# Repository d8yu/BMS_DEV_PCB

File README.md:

<h1>BMS Development Board</h1>

<h2>Preview</h2>
<h3>PCB Schematic</h3>

<h3>PCB Render</h3>

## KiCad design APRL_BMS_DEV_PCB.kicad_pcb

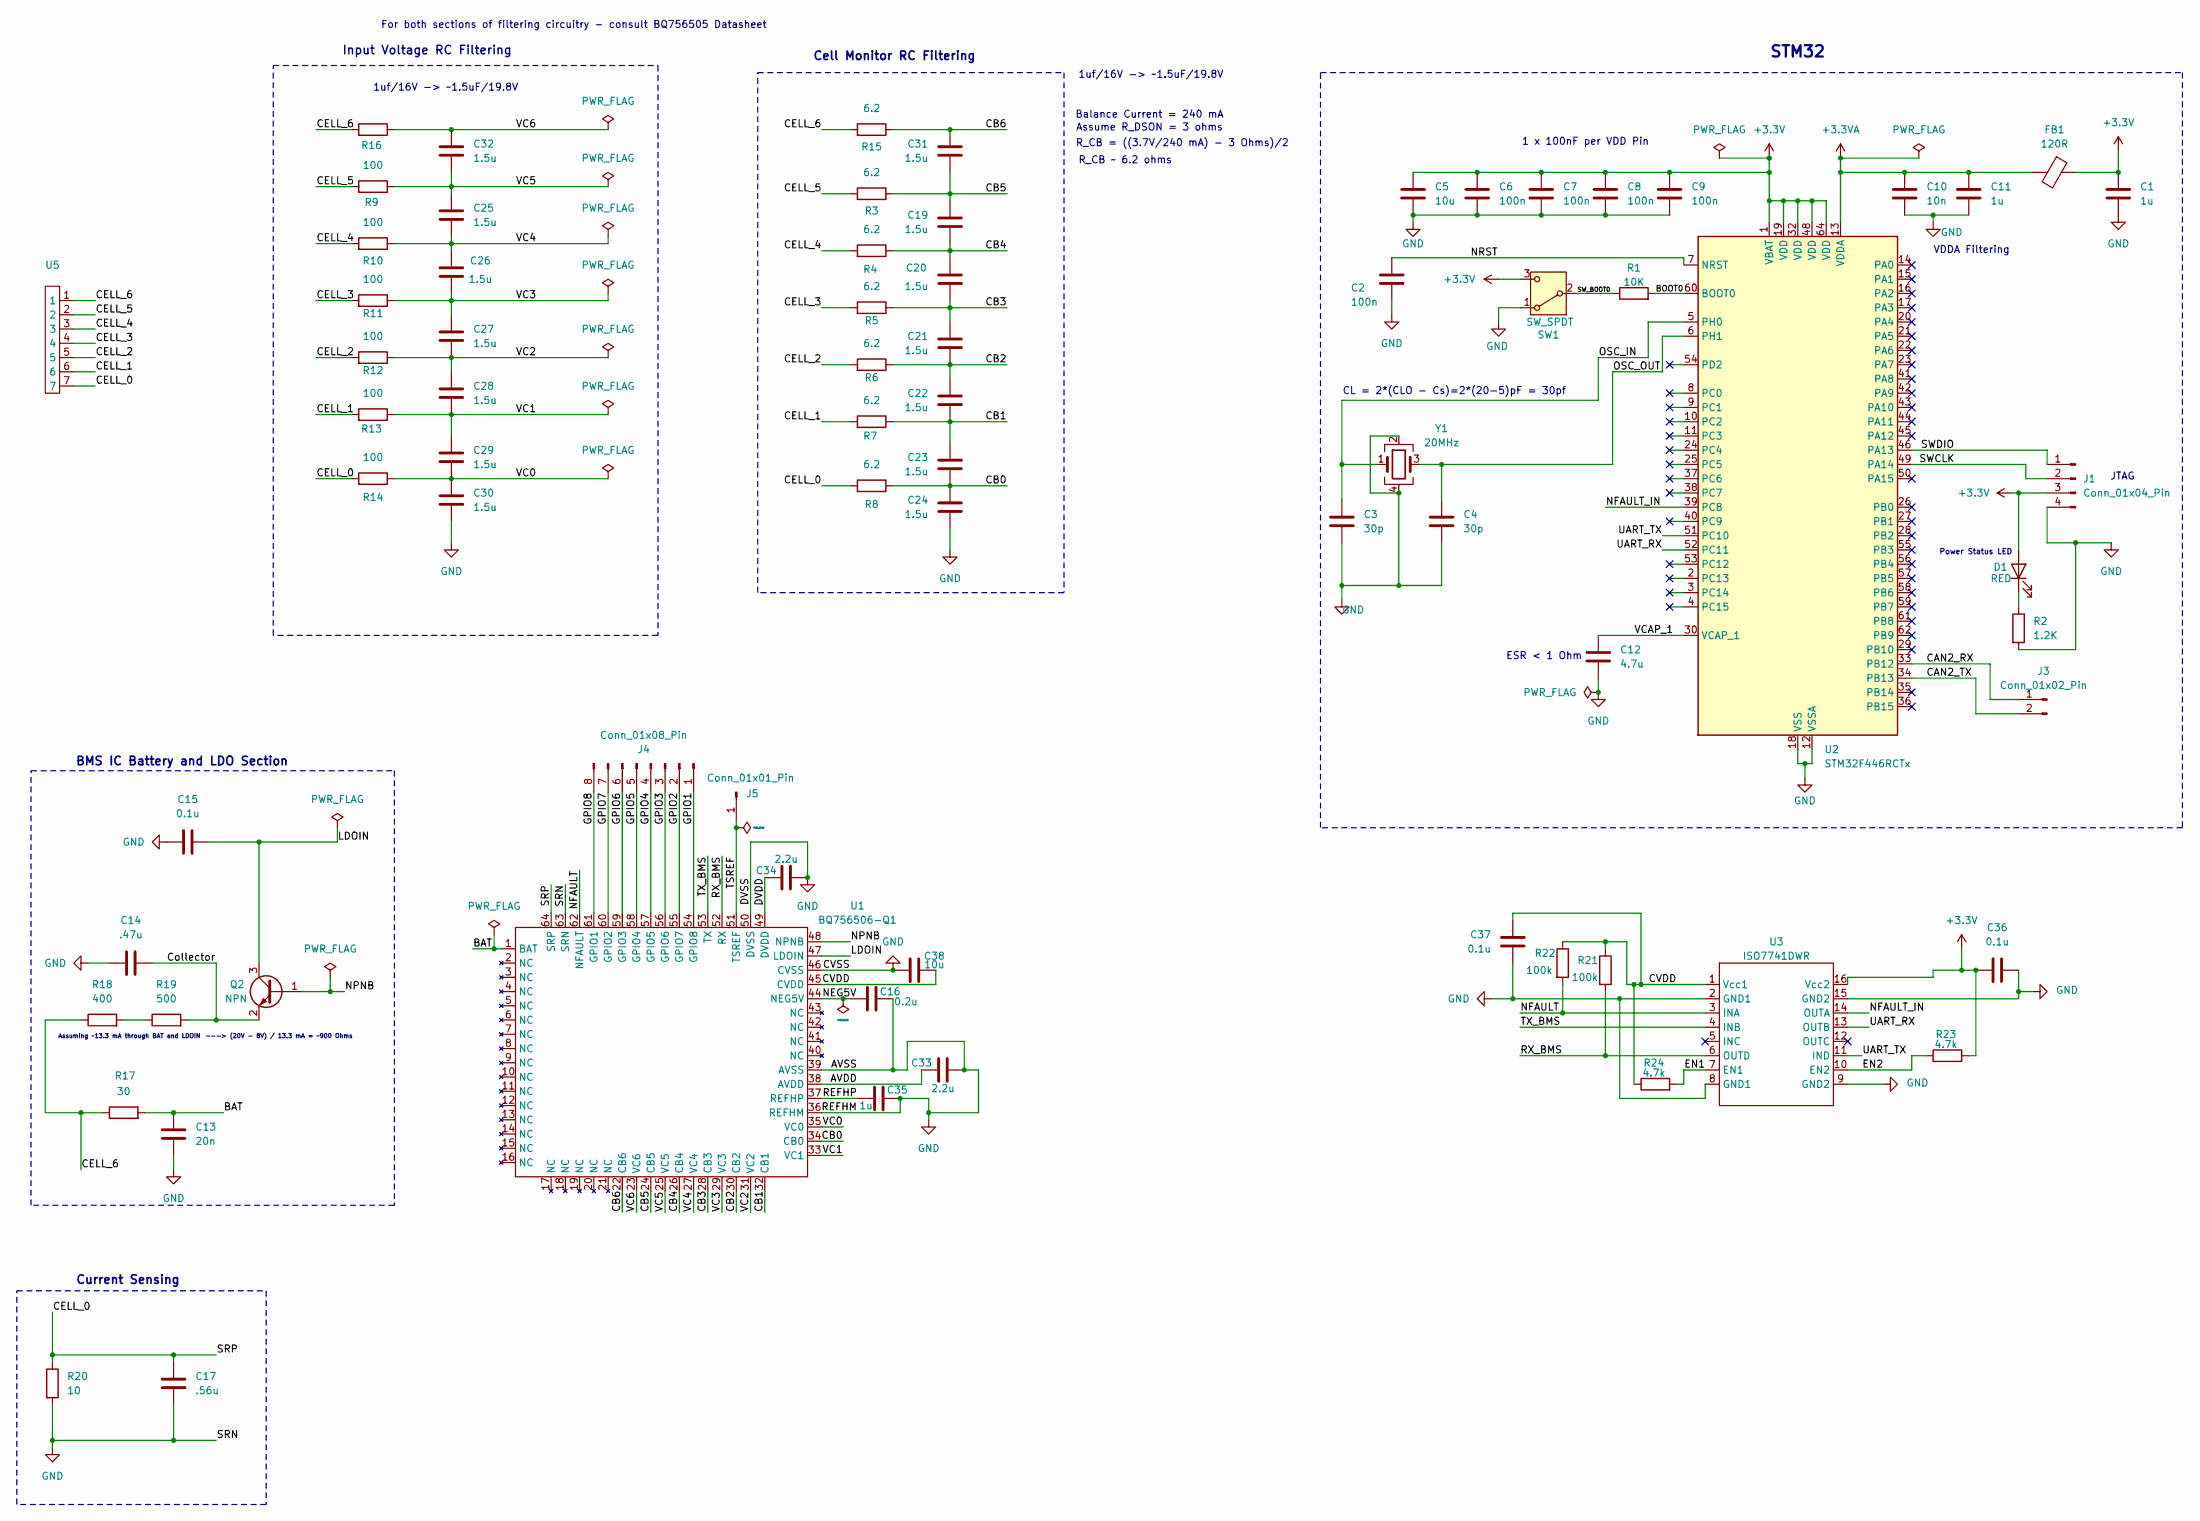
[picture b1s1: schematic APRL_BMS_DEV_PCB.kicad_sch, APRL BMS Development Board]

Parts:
C1, C11, C35: 1u; C_0603_1608Metric
C2, C6, C7, C8, C9: 100n; C_0603_1608Metric
C3, C4: 30p; C_0603_1608Metric
C5, C38: 10u; C_0603_1608Metric
C10: 10n; C_0603_1608Metric
C12: 4.7u; C_0603_1608Metric
C13: 20n; C_0603_1608Metric
C14: .47u; C_0603_1608Metric
C15, C36, C37: 0.1u; C_0603_1608Metric
C16: 0.2u; C_0603_1608Metric
C17: .56u; C_0603_1608Metric
C19, C20, C21, C22, C23, C24, C25, C26, C27, C28, C29, C30, C31, C32: 1.5u; C_0402_1005Metric
C33, C34: 2.2u; C_0603_1608Metric
D1: RED; LED_0603_1608Metric
FB1: 120R; R_0603_1608Metric
J1: Conn_01x04_Pin; PinHeader_1x04_P2.54mm_Vertical
J3: Conn_01x02_Pin; PinHeader_1x02_P2.54mm_Vertical
J4: Conn_01x08_Pin; PinHeader_1x08_P2.54mm_Vertical
J5: Conn_01x01_Pin; PinHeader_1x01_P2.54mm_Vertical
Q2: NPN; SOT-23
R1: 10K; R_0603_1608Metric
R2: 1.2K; R_0603_1608Metric
R3, R4, R5, R6, R7, R8, R15: 6.2; R_0603_1608Metric
R9, R10, R11, R12, R13, R14, R16: 100; R_0603_1608Metric
R17: 30; R_0603_1608Metric
R18: 400; R_0603_1608Metric
R19: 500; R_0603_1608Metric
R20: 10; R_0603_1608Metric
R21, R22: 100k; R_0603_1608Metric
R23, R24: 4.7k; R_0603_1608Metric
SW1: SW_SPDT; SW_SPDT_PCM12
U1: BQ756506-Q1; LQFP-64_10x10mm_P0.5mm
U2: STM32F446RCTx; LQFP-64_10x10mm_P0.5mm
U3: ISO7741DWR; SOIC-16W_5.3x10.2mm_P1.27mm
U5: S7B-XH-A-1
Y1: 20MHz; Crystal_SMD_3225-4Pin_3.2x2.5mm

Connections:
+3.3V: C1.1, C5.1, C6.1, C7.1, C8.1, C9.1, C36.1, D1.2 (A), FB1.1, J1.3, R23.2, SW1.3 (C), U2.1 (VBAT), U2.19 (VDD), U2.32 (VDD), U2.48 (VDD), U2.64 (VDD), U3.16 (Vcc2)
+3.3VA: C10.1, C11.1, FB1.2, U2.13 (VDDA)
/AVDD: C33.2, U1.38 (AVDD)
/BAT: C13.1, R17.2, U1.1 (BAT)
/BOOT0: R1.2, U2.60 (BOOT0)
/CAN2_RX: J3.1, U2.33 (PB12)
/CAN2_TX: J3.2, U2.34 (PB13)
/CB0: C23.2, C24.1, R8.1, U1.34 (CB0)
/CB1: C22.2, C23.1, R7.1, U1.32 (CB1)
/CB2: C21.2, C22.1, R6.1, U1.30 (CB2)
/CB3: C20.2, C21.1, R5.1, U1.28 (CB3)
/CB4: C19.2, C20.1, R4.1, U1.26 (CB4)
/CB5: C19.1, C31.2, R3.1, U1.24 (CB5)
/CB6: C31.1, R15.1, U1.22 (CB6)
/CELL_0: C17.1, R8.2, R14.2, R20.1, U1.64 (SRP), U5.7
/CELL_1: R7.2, R13.2, U5.6
/CELL_2: R6.2, R12.2, U5.5
/CELL_3: R5.2, R11.2, U5.4
/CELL_4: R4.2, R10.2, U5.3
/CELL_5: R3.2, R9.2, U5.2
/CELL_6: R15.2, R16.2, R17.1, R18.1, U5.1
/CVDD: C37.1, C38.2, R21.1, R22.1, R24.1, U1.45 (CVDD), U3.1 (Vcc1)
/Collector: C14.2, Q2.2 (E), R19.2
/DVDD: C34.1, U1.49 (DVDD)
/EN1: R24.2, U3.7 (EN1)
/EN2: R23.1, U3.10 (EN2)
/GPIO1: J4.1, U1.54 (GPIO8)
/GPIO2: J4.2, U1.55 (GPIO7)
/GPIO3: J4.3, U1.56 (GPIO6)
/GPIO4: J4.4, U1.57 (GPIO5)
/GPIO5: J4.5, U1.58 (GPIO4)
/GPIO6: J4.6, U1.59 (GPIO3)
/GPIO7: J4.7, U1.60 (GPIO2)
/GPIO8: J4.8, U1.61 (GPIO1)
/LDOIN: C15.2, Q2.3 (C), U1.47 (LDOIN)
/NEG5V: C16.2, U1.44 (NEG5V)
/NFAULT: R22.2, U1.62 (NFAULT), U3.3 (INA)
/NFAULT_IN: U2.39 (PC8), U3.14 (OUTA)
/NPNB: Q2.1 (B), U1.48 (NPNB)
/NRST: C2.1, U2.7 (NRST)
/OSC_IN: C3.1, U2.5 (PH0), Y1.1
/OSC_OUT: C4.1, U2.6 (PH1), Y1.3
/REFHP: C35.2, U1.37 (REFHP)
/RX_BMS: R21.2, U1.52 (RX), U3.6 (OUTD)
/SWCLK: J1.2, U2.49 (PA14)
/SWDIO: J1.1, U2.46 (PA13)
/SW_BOOT0: R1.1, SW1.2 (B)
/TSREF: J5.1, U1.51 (TSREF)
/TX_BMS: U1.53 (TX), U3.4 (INB)
/UART_RX: U2.52 (PC11), U3.13 (OUTB)
/UART_TX: U2.51 (PC10), U3.11 (IND)
/VC0: C29.2, C30.1, R14.1, U1.35 (VC0)
/VC1: C28.2, C29.1, R13.1, U1.33 (VC1)
/VC2: C27.2, C28.1, R12.1, U1.31 (VC2)
/VC3: C26.2, C27.1, R11.1, U1.29 (VC3)
/VC4: C25.2, C26.1, R10.1, U1.27 (VC4)
/VC5: C25.1, C32.2, R9.1, U1.25 (VC5)
/VC6: C32.1, R16.1, U1.23 (VC6)
/VCAP_1: C12.1, U2.30 (VCAP_1)
GND: C1.2, C2.2, C3.2, C4.2, C5.2, C6.2, C7.2, C8.2, C9.2, C10.2, C11.2, C12.2, C13.2, C14.1, C15.1, C16.1, C17.2, C24.2, C30.2, C33.1, C34.2, C35.1, C36.2, C37.2, C38.1, J1.4, R2.2, R20.2, SW1.1 (A), U1.36 (REFHM), U1.39 (AVSS), U1.46 (CVSS), U1.50 (DVSS), U1.63 (SRN), U2.12 (VSSA), U2.18 (VSS), U2.31 (VSS), U2.47 (VSS), U2.63 (VSS), U3.2 (GND1), U3.8 (GND1), U3.9 (GND2), U3.15 (GND2), Y1.2, Y1.4
unnamed: D1.1 (K), R2.1
unnamed: R18.2, R19.1

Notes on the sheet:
VDDA Filtering
1uf/16V -> ~1.5uF/19.8V
Balance Current = 240 mA
R_CB = ((3.7V/240 mA) - 3 Ohms)/2
Power Status LED
Assume R_DSON = 3 ohms
JTAG
BMS IC Battery and LDO Section
Assuming ~13.3 mA through BAT and LDOIN
For both sections of filtering circuitry - consult BQ756505 Datasheet
1 x 100nF per VDD Pin
CL = 2*(CLO - Cs)=2*(20-5)pF = 30pf
ESR < 1 Ohm
---> (20V - 8V) / 13.3 mA = ~900 Ohms
STM32
Input Voltage RC Filtering
R_CB ~ 6.2 ohms
Cell Monitor RC Filtering
Current Sensing

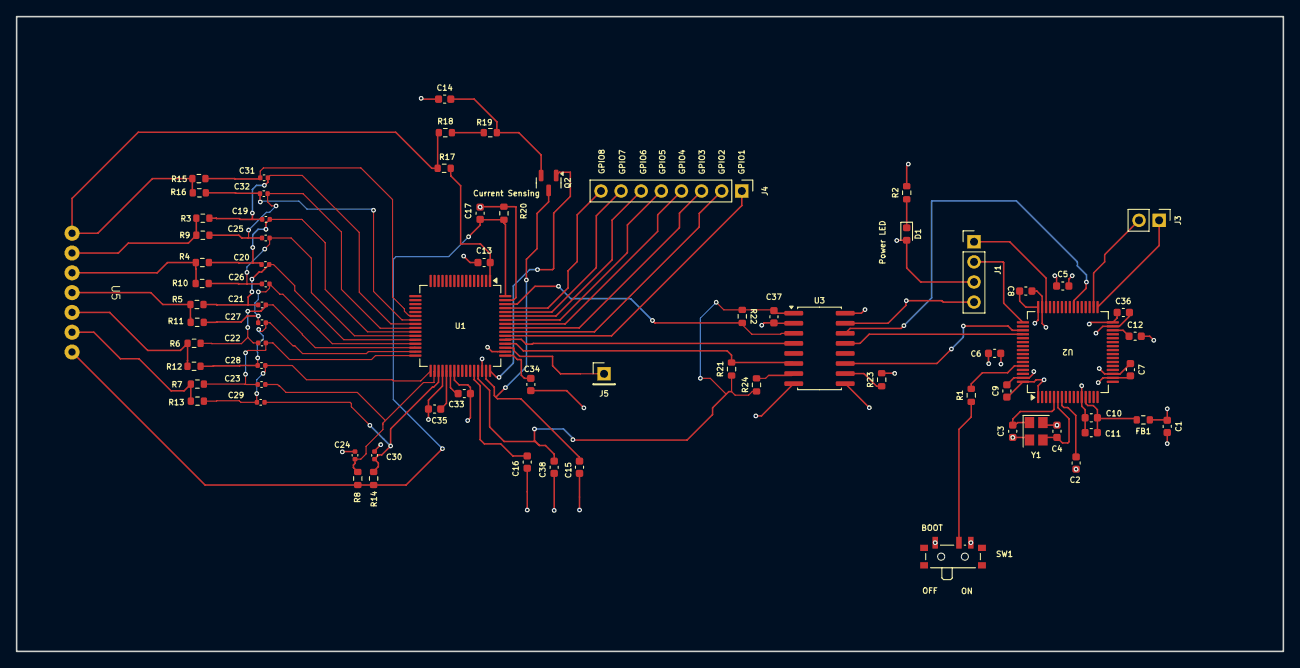
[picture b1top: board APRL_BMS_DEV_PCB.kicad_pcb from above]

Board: 4 copper layers, 160.0 x 80.2 mm, 74 parts (0 on the bottom side), 62 nets.

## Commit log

2025-04-24 Added Initial Files
2025-04-24 Initial Laptop Push Test
2025-04-24 Laptop Push Test
2025-04-24 Initial configuration for STM32
2025-04-25 More
2025-04-25 Updated stuff
2025-04-25 Create Hello
2025-04-25 Git Test
2025-04-25 fixed Git
2025-04-25 Vanilla Values
2025-04-27 Some added pinout
2025-04-27 Changed schematic size to A3
2025-04-28 Added RC Filtering
2025-04-28 Added more labeling to RC filtering
2025-04-28 Added New Net Labels to RC Filters
2025-04-28 Added a TO DO file
2025-04-29 Added initial power circuitry
2025-04-29 Updated To-Do
2025-04-30 Bash_Script
2025-04-30 Hello World
2025-04-30 Added Isolation IC
2025-05-03 Added initial footprints and values for caps
2025-05-04 Calculated R and C values, added footprints
2025-05-04 blank
2025-05-08 added gnd to isolator
2025-05-09 Fixed most ERC errors, waiting for response on Isolator configuration
2025-05-10 Edited PCB a little
2025-05-11 Added PCB Traces, fixed Digital Isolator
2025-05-13 Refined some traces
2025-05-15 Fixed TX and RX Trace distances
2025-05-15 Started routing Vias for voltage sensing pins
2025-05-15 Changed trace width for signals to 0.15mm
2025-05-16 Finished sketching traces - save for NPN
2025-05-17 Finished initial trace.
2025-05-17 Fixed silkscreen
2025-06-02 Initial design COMPLETE!
2025-08-24 Organized Files
